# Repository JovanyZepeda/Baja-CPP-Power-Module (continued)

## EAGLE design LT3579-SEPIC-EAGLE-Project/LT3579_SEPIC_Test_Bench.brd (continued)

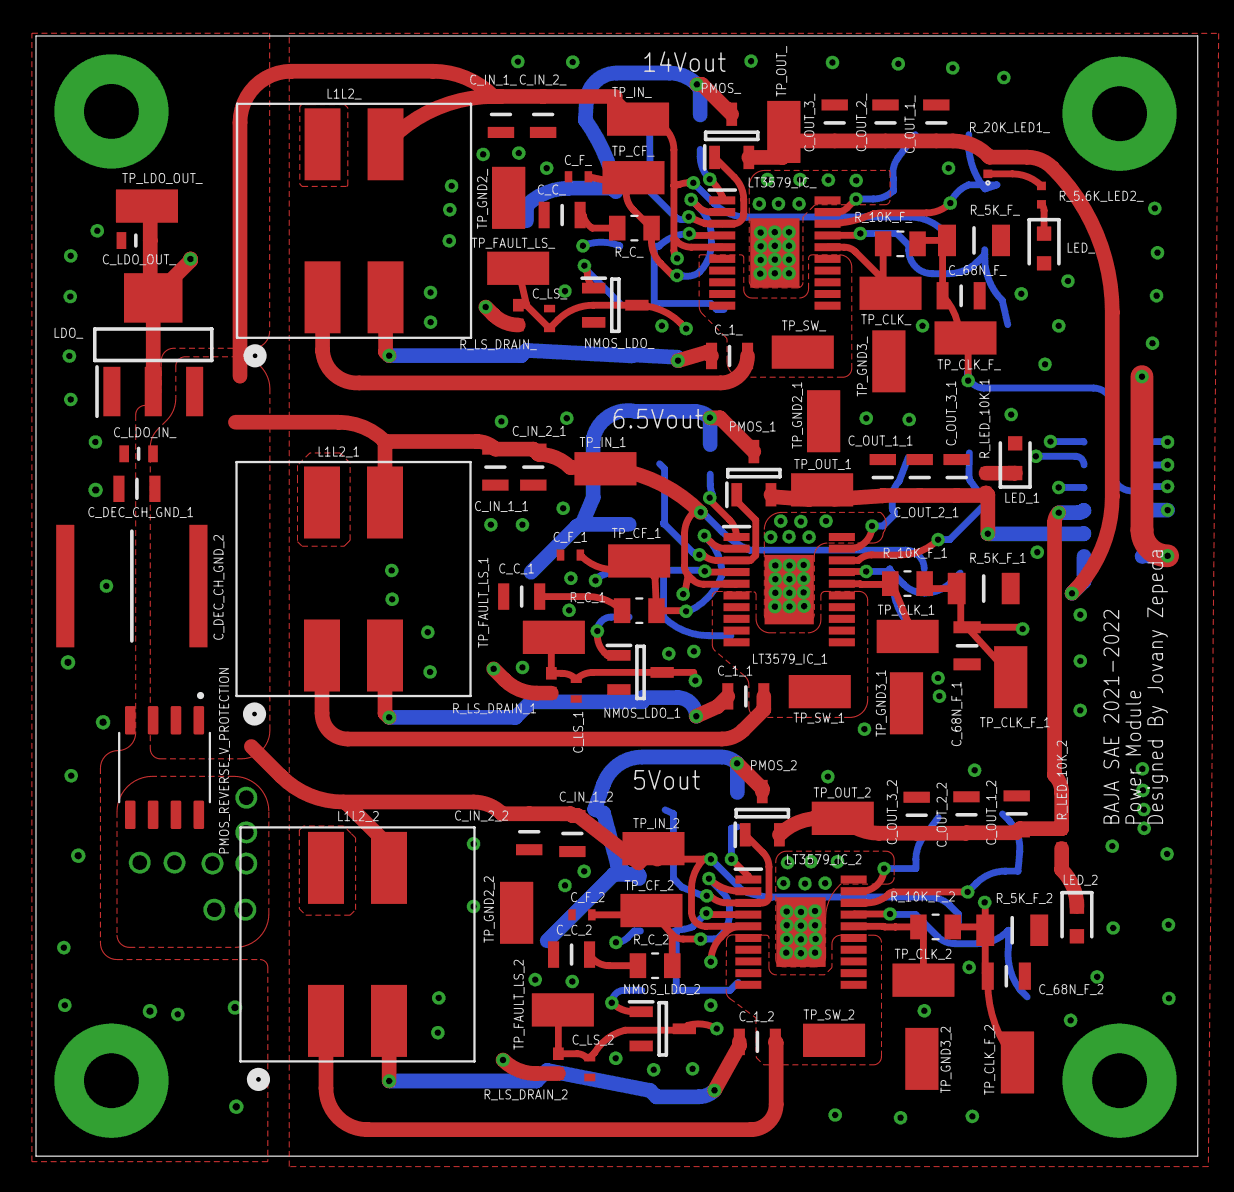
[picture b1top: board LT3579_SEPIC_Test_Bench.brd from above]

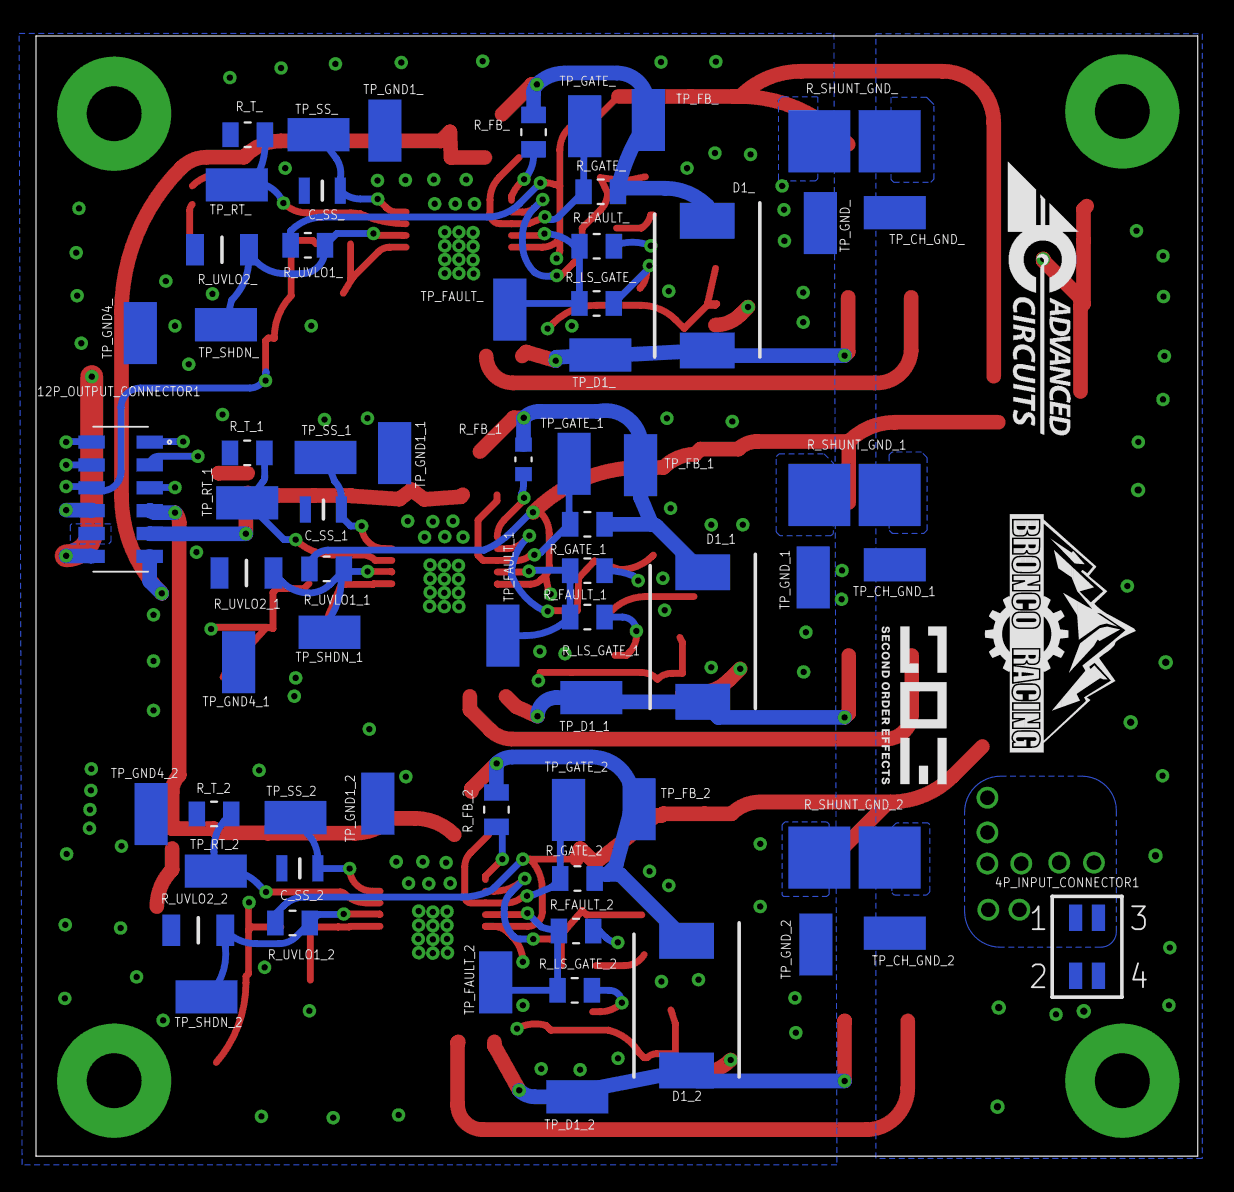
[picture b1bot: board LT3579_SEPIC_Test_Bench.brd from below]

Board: 4 copper layers, 64.5 x 62.2 mm, 164 parts (65 on the bottom side), 57 nets.

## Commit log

2022-02-13 First Commit
    q
2022-02-13 added files to be ignored
2022-02-13 Testing and playing around with simulation. High Current Spikes still present
2022-02-14 Discover new diode MBRS360 works better. Continue ahead in choosing parts.
2022-02-18 Updated net names
2022-02-19 Made new files for short circuit and undervoltage lockout testing
2022-02-24 Added new sims and ignored more files
2022-02-25 made new schematic for input inductance
2022-02-25 Added new files for simulating wire inductance
2022-02-26 Updated circuit
2022-02-28 updated to exclude files from subdirectories
2022-02-28 Moved files into new subdirectories
2022-02-28 Created two new files for 5Vout and 6.5Vout sepic converters
2022-02-28 updated simulations to account for availiable componant values
2022-03-05 added undervoltage and short circuit test for vout 6.5 and 5vout
2022-03-06 started PCB design
2022-03-17 Modfied EAGLE schematic
2022-03-17 Modified Schematic EAGLE
2022-03-18 Added Custom Libraries
2022-03-18 Added New Libraries and modified schematic
2022-03-19 Modfied Schematics
2022-03-19 Modified Eagle Project and Schematic
2022-03-19 Modfied Schematic files eagle
2022-03-19 Modified Library Files
2022-03-20 Added Board Layout. Initial Board Layout done.
2022-03-21 Added new componants and files
2022-03-21 new files
2022-03-29 Removed and replaced files
2022-04-07 Added and Replaced new files
2022-04-09 Added new FIles
2022-04-09 added files
2022-04-27 LAPTOP: Updated files from other repo and copied them here.
